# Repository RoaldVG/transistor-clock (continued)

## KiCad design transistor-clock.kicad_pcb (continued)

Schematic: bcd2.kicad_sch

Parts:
U5, U6: flipflop; module_flipflop_mpcie; LCSC Part # C185937

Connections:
+3V3: U5.21 (J), U5.25 (K), U6.21 (J), U6.25 (K); also elsewhere on the board
/counters/BCD_h0/Clr: U5.23 (Clk); also elsewhere on the board
/counters/BCD_h1/Clr: U5.29 (Clr), U6.29 (Clr), U6.31 (Q); also elsewhere on the board
/counters/BCD_h1/Q0: U5.31 (Q), U6.23 (Clk); also elsewhere on the board

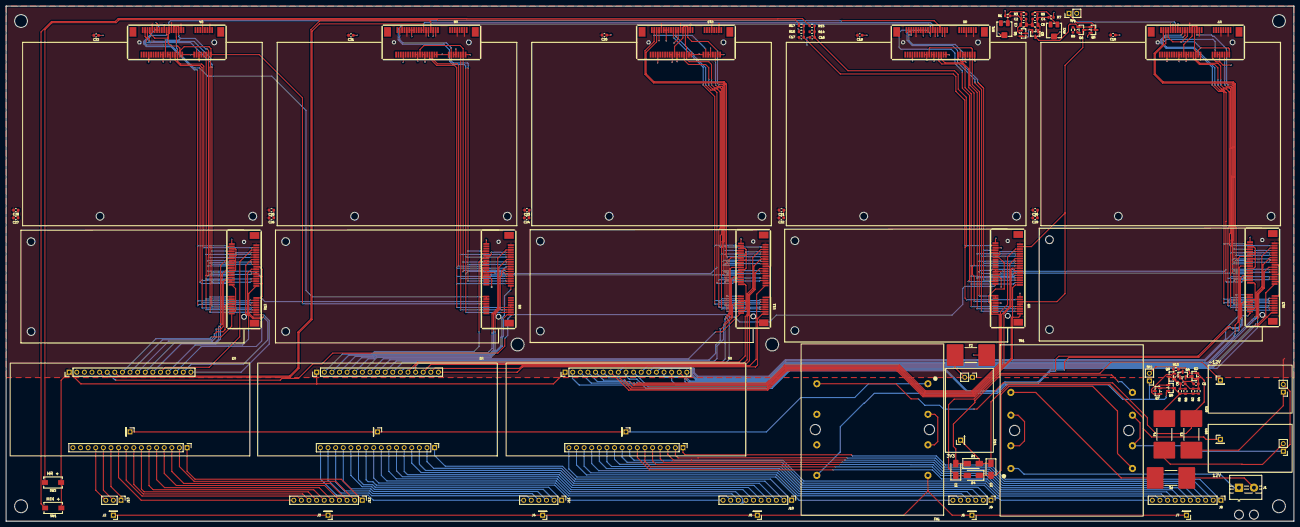
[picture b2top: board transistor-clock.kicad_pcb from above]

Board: 2 copper layers, 430.0 x 172.0 mm, 97 parts (0 on the bottom side), 174 nets.

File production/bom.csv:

Designator,Footprint,Quantity,Value,LCSC Part #
"C1, C6",0603,2,10n,C57112
"C16, C17, C18, C19, C20, C21, C22",0603,7,100n,C14663
"C2, C4",0603,2,1u,C15849
"C23, C24, C25, C26, C27, C28, C29, C30, C31, C32",0603,10,10u,C19702
"C3, C5",0805,2,47u,C16780
"D1, D2, D3, D4",D_SMA,4,S3MF,C64874
"F1, F3, F4",Fuse_Littelfuse-NANO2-885,3,250mA?,C41371860
F2,Fuse_Littelfuse-NANO2-885,1,2A?,C41371860
J1,TerminalBlock_MaiXu_MX126-5.0-02P_1x02_P5.00mm,1,Screw_Terminal_01x02,
"Q1, Q2, Q3, Q4, Q9",SOT-23,5,MMBT3904,C20526v
"Q5, Q7",SOT-23,2,AO3401A,C15127
"Q6, Q8",SOT-23,2,2N7002,C8545
"R1, R2, R3, R5, R7, R8",0603,6,15k,C22809
"R10, R15, R17, R9",0603,4,1k,C21190
"R14, R16",0603,2,10k,C25804
"R4, R6",0603,2,120k,C25808
"RV1, RV2",Potentiometer_Bourns_3214J_Horizontal,2,5k,C58391
SW1,SW_SPST_EVQPE1,1,MIN +,C720477
SW2,SW_SPST_EVQPE1,1,HR +,C720477
TP1,PinHeader_1x02_P2.54mm_Vertical,1,TestPoint_2Pole,
"U1, U2, U3",module_ssr,3,SSR,
"U10, U4, U5, U6, U7",module_flipflop_mpcie,5,flipflop,C185937
"U11, U12, U13, U8, U9",module_bdc_mpcie,5,bin-to-dec,C185937
U14,module_PSU,1,3V3,
U15,module_PSU,1,12V,
U16,module_PSU,1,-12V,

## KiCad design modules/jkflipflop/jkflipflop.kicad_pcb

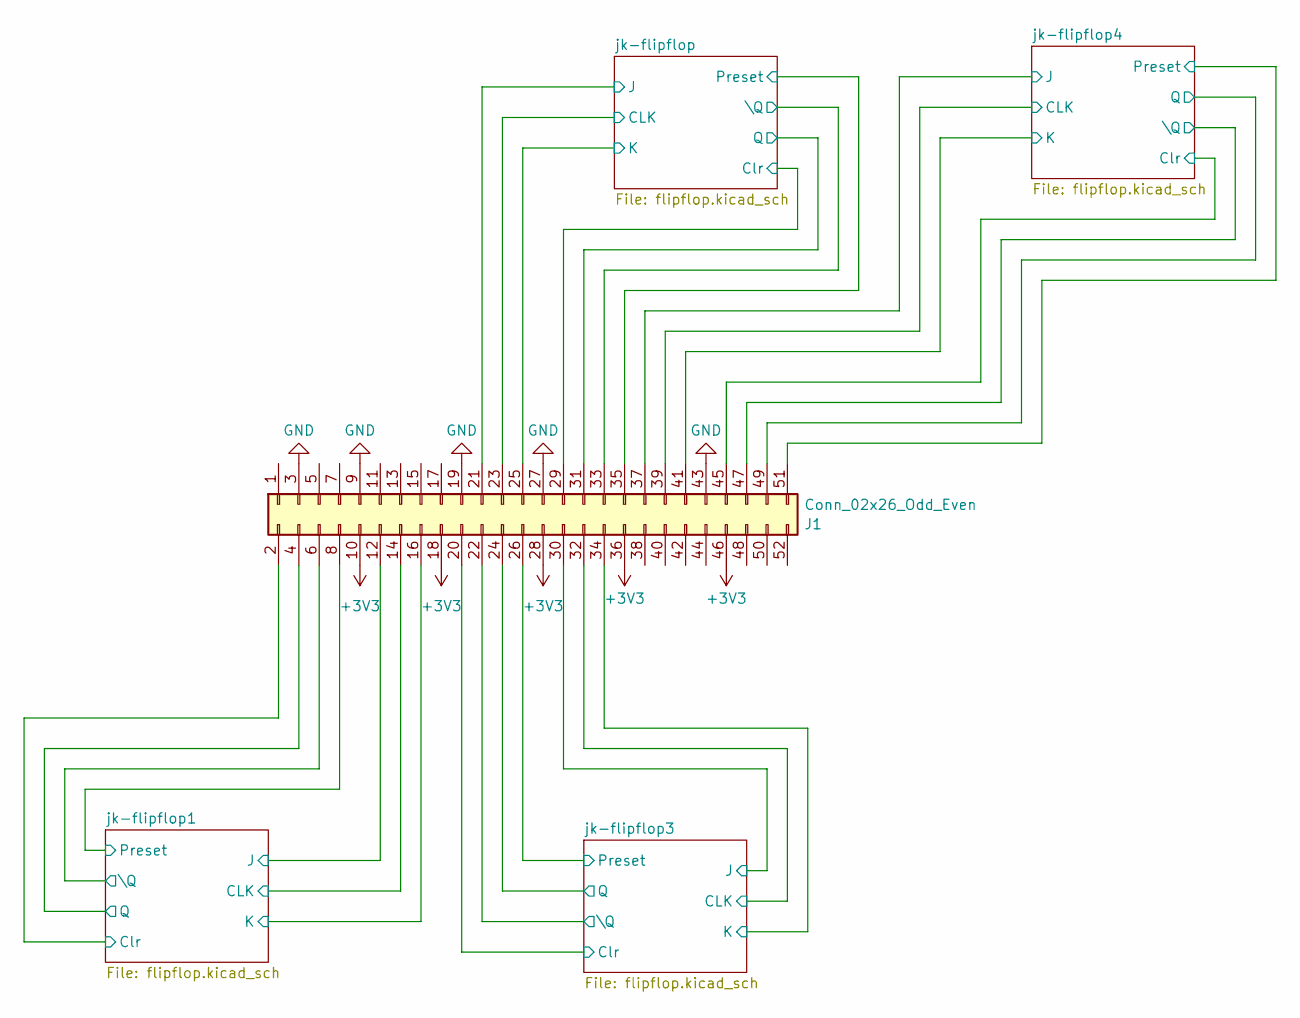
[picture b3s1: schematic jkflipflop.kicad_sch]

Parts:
J1: Conn_02x26_Odd_Even; mpcie-full-card

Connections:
+3V3: J1.10, J1.18, J1.28, J1.36, J1.46; also elsewhere on the board
/jk-flipflop1/CLK: J1.14; also elsewhere on the board
/jk-flipflop1/Clr: J1.2; also elsewhere on the board
/jk-flipflop1/J: J1.12; also elsewhere on the board
/jk-flipflop1/K: J1.16; also elsewhere on the board
/jk-flipflop1/Preset: J1.8; also elsewhere on the board
/jk-flipflop1/Q: J1.4; also elsewhere on the board
/jk-flipflop1/\Q: J1.6; also elsewhere on the board
/jk-flipflop3/CLK: J1.32; also elsewhere on the board
/jk-flipflop3/Clr: J1.20; also elsewhere on the board
/jk-flipflop3/J: J1.30; also elsewhere on the board
/jk-flipflop3/K: J1.34; also elsewhere on the board
/jk-flipflop3/Preset: J1.26; also elsewhere on the board
/jk-flipflop3/Q: J1.24; also elsewhere on the board
/jk-flipflop3/\Q: J1.22; also elsewhere on the board
/jk-flipflop4/CLK: J1.39; also elsewhere on the board
/jk-flipflop4/Clr: J1.45; also elsewhere on the board
/jk-flipflop4/J: J1.37; also elsewhere on the board
/jk-flipflop4/K: J1.41; also elsewhere on the board
/jk-flipflop4/Preset: J1.51; also elsewhere on the board
/jk-flipflop4/Q: J1.49; also elsewhere on the board
/jk-flipflop4/\Q: J1.47; also elsewhere on the board
/jk-flipflop/CLK: J1.23; also elsewhere on the board
/jk-flipflop/Clr: J1.29; also elsewhere on the board
/jk-flipflop/J: J1.21; also elsewhere on the board
/jk-flipflop/K: J1.25; also elsewhere on the board
/jk-flipflop/Preset: J1.35; also elsewhere on the board
/jk-flipflop/Q: J1.31; also elsewhere on the board
/jk-flipflop/\Q: J1.33; also elsewhere on the board
GND: J1.3, J1.9, J1.19, J1.27, J1.43; also elsewhere on the board

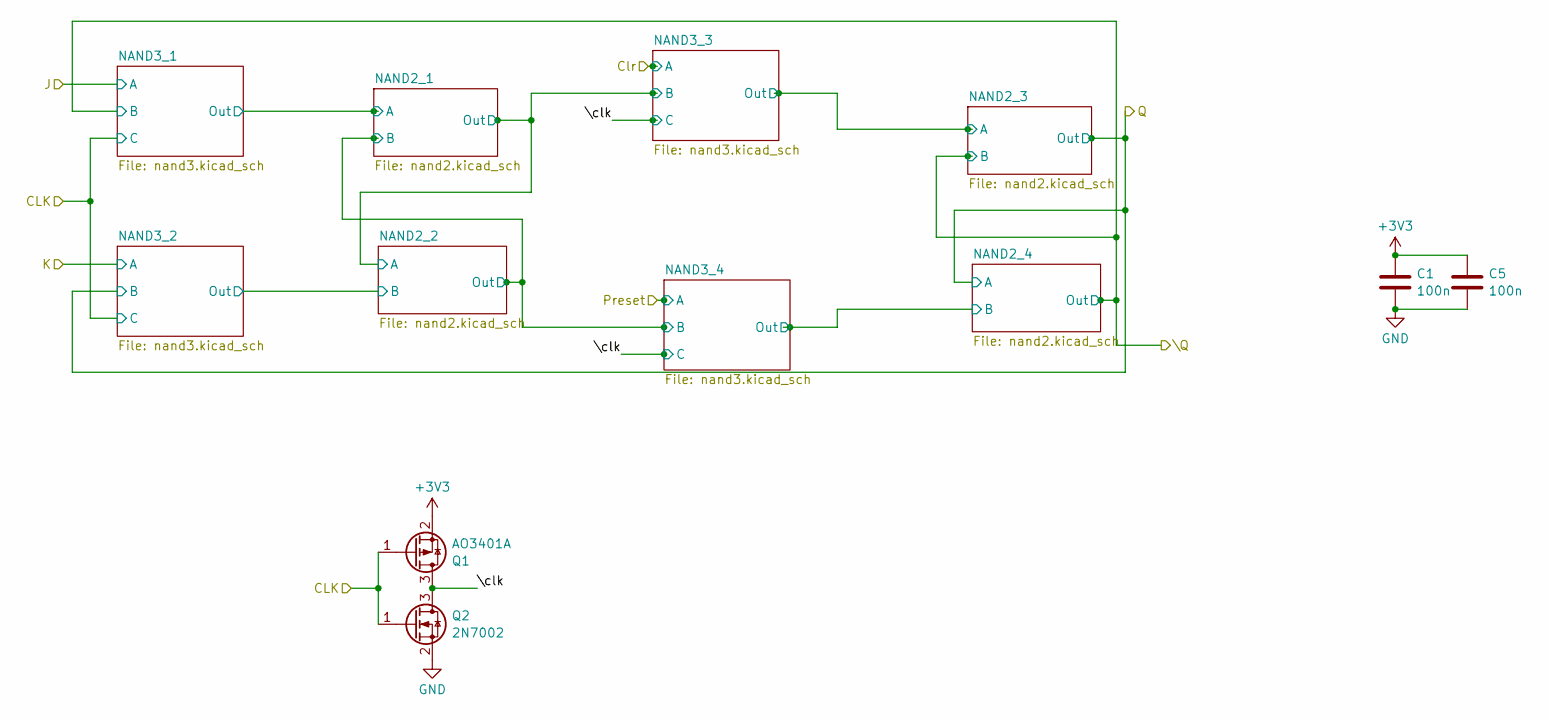
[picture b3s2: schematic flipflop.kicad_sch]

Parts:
C1, C5: 100n; C_0603_1608Metric; LCSC Part # C14663
Q1: AO3401A; SOT-23; LCSC Part # C15127
Q2: 2N7002; SOT-23; LCSC Part # C8545

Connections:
+3V3: C1.1, C5.1, Q1.2 (S); also elsewhere on the board
/jk-flipflop1/CLK: Q1.1 (G), Q2.1 (G); also elsewhere on the board
/jk-flipflop1/\clk: Q1.3 (D), Q2.3 (D); also elsewhere on the board
GND: C1.2, C5.2, Q2.2 (S); also elsewhere on the board

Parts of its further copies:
C2, C3, C4, C6, C7, C8: 100n; C_0603_1608Metric; LCSC Part # C14663
Q21, Q57, Q77: AO3401A; SOT-23; LCSC Part # C15127
Q22, Q58, Q78: 2N7002; SOT-23; LCSC Part # C8545

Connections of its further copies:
+3V3: C2.1, C3.1, C4.1, C6.1, C7.1, C8.1, Q21.2 (S), Q57.2 (S), Q77.2 (S); also elsewhere on the board
/jk-flipflop3/CLK: Q77.1 (G), Q78.1 (G); also elsewhere on the board
/jk-flipflop3/\clk: Q77.3 (D), Q78.3 (D); also elsewhere on the board
/jk-flipflop4/CLK: Q57.1 (G), Q58.1 (G); also elsewhere on the board
/jk-flipflop4/\clk: Q57.3 (D), Q58.3 (D); also elsewhere on the board
/jk-flipflop/CLK: Q21.1 (G), Q22.1 (G); also elsewhere on the board
/jk-flipflop/\clk: Q21.3 (D), Q22.3 (D); also elsewhere on the board
GND: C2.2, C3.2, C4.2, C6.2, C7.2, C8.2, Q22.2 (S), Q58.2 (S), Q78.2 (S); also elsewhere on the board

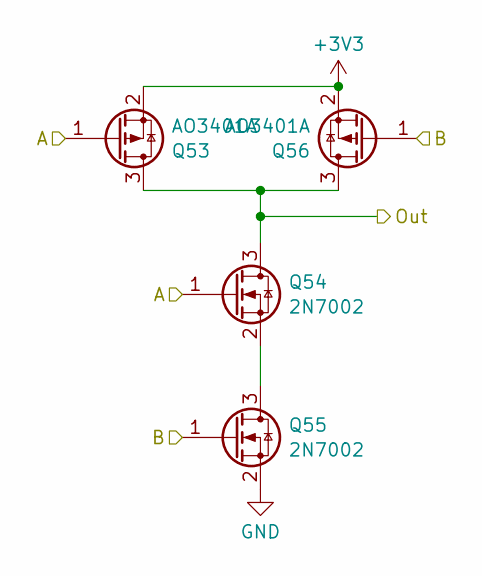
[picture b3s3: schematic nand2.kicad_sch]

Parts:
Q53, Q56: AO3401A; SOT-23; LCSC Part # C15127
Q54, Q55: 2N7002; SOT-23; LCSC Part # C8545

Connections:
+3V3: Q53.2 (S), Q56.2 (S); also elsewhere on the board
/jk-flipflop1/NAND2_1/B: Q53.3 (D), Q54.3 (D), Q56.3 (D); also elsewhere on the board
/jk-flipflop1/NAND2_1/Out: Q53.1 (G), Q54.1 (G); also elsewhere on the board
/jk-flipflop1/NAND2_2/B: Q55.1 (G), Q56.1 (G); also elsewhere on the board
GND: Q55.2 (S); also elsewhere on the board
unnamed: Q54.2 (S), Q55.3 (D)

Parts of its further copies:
Q104, Q111, Q113, Q116, Q117, Q120, Q121, Q124, Q125, Q128, Q129, Q132, Q133, Q136, Q137, Q140, Q141, Q144, Q145, Q148, Q149, Q152, Q153, Q156, Q157, Q160, Q161, Q164, Q165, Q168: AO3401A; SOT-23; LCSC Part # C15127
Q108, Q109, Q114, Q115, Q118, Q119, Q122, Q123, Q126, Q127, Q130, Q131, Q134, Q135, Q138, Q139, Q142, Q143, Q146, Q147, Q150, Q151, Q154, Q155, Q158, Q159, Q162, Q163, Q166, Q167: 2N7002; SOT-23; LCSC Part # C8545

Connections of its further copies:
+3V3: Q104.2 (S), Q111.2 (S), Q113.2 (S), Q116.2 (S), Q117.2 (S), Q120.2 (S), Q121.2 (S), Q124.2 (S), Q125.2 (S), Q128.2 (S), Q129.2 (S), Q132.2 (S), Q133.2 (S), Q136.2 (S), Q137.2 (S), Q140.2 (S), Q141.2 (S), Q144.2 (S), Q145.2 (S), Q148.2 (S), Q149.2 (S), Q152.2 (S), Q153.2 (S), Q156.2 (S), Q157.2 (S), Q160.2 (S), Q161.2 (S), Q164.2 (S), Q165.2 (S), Q168.2 (S); also elsewhere on the board
/jk-flipflop1/NAND2_1/A: Q157.1 (G), Q158.1 (G); also elsewhere on the board
/jk-flipflop1/NAND2_1/B: Q159.1 (G), Q160.1 (G); also elsewhere on the board
/jk-flipflop1/NAND2_1/Out: Q157.3 (D), Q158.3 (D), Q160.3 (D); also elsewhere on the board
/jk-flipflop1/NAND2_3/A: Q125.1 (G), Q126.1 (G); also elsewhere on the board
/jk-flipflop1/NAND2_4/B: Q131.1 (G), Q132.1 (G); also elsewhere on the board
/jk-flipflop1/Q: Q125.3 (D), Q126.3 (D), Q128.3 (D), Q129.1 (G), Q130.1 (G); also elsewhere on the board
/jk-flipflop1/\Q: Q127.1 (G), Q128.1 (G), Q129.3 (D), Q130.3 (D), Q132.3 (D); also elsewhere on the board
/jk-flipflop3/NAND2_1/A: Q161.1 (G), Q162.1 (G); also elsewhere on the board
/jk-flipflop3/NAND2_1/B: Q121.3 (D), Q122.3 (D), Q124.3 (D), Q163.1 (G), Q164.1 (G); also elsewhere on the board
/jk-flipflop3/NAND2_1/Out: Q121.1 (G), Q122.1 (G), Q161.3 (D), Q162.3 (D), Q164.3 (D); also elsewhere on the board
/jk-flipflop3/NAND2_2/B: Q123.1 (G), Q124.1 (G); also elsewhere on the board
/jk-flipflop3/NAND2_3/A: Q149.1 (G), Q150.1 (G); also elsewhere on the board
/jk-flipflop3/NAND2_4/B: Q155.1 (G), Q156.1 (G); also elsewhere on the board
/jk-flipflop3/Q: Q149.3 (D), Q150.3 (D), Q152.3 (D), Q153.1 (G), Q154.1 (G); also elsewhere on the board
/jk-flipflop3/\Q: Q151.1 (G), Q152.1 (G), Q153.3 (D), Q154.3 (D), Q156.3 (D); also elsewhere on the board
/jk-flipflop4/NAND2_1/A: Q165.1 (G), Q166.1 (G); also elsewhere on the board
/jk-flipflop4/NAND2_1/B: Q117.3 (D), Q118.3 (D), Q120.3 (D), Q167.1 (G), Q168.1 (G); also elsewhere on the board
/jk-flipflop4/NAND2_1/Out: Q117.1 (G), Q118.1 (G), Q165.3 (D), Q166.3 (D), Q168.3 (D); also elsewhere on the board
/jk-flipflop4/NAND2_2/B: Q119.1 (G), Q120.1 (G); also elsewhere on the board
/jk-flipflop4/NAND2_3/A: Q141.1 (G), Q142.1 (G); also elsewhere on the board
/jk-flipflop4/NAND2_4/B: Q147.1 (G), Q148.1 (G); also elsewhere on the board
/jk-flipflop4/Q: Q141.3 (D), Q142.3 (D), Q144.3 (D), Q145.1 (G), Q146.1 (G); also elsewhere on the board
/jk-flipflop4/\Q: Q143.1 (G), Q144.1 (G), Q145.3 (D), Q146.3 (D), Q148.3 (D); also elsewhere on the board
/jk-flipflop/NAND2_1/A: Q104.1 (G), Q108.1 (G); also elsewhere on the board
/jk-flipflop/NAND2_1/B: Q109.1 (G), Q111.1 (G), Q113.3 (D), Q114.3 (D), Q116.3 (D); also elsewhere on the board
/jk-flipflop/NAND2_1/Out: Q104.3 (D), Q108.3 (D), Q111.3 (D), Q113.1 (G), Q114.1 (G); also elsewhere on the board
/jk-flipflop/NAND2_2/B: Q115.1 (G), Q116.1 (G); also elsewhere on the board
/jk-flipflop/NAND2_3/A: Q133.1 (G), Q134.1 (G); also elsewhere on the board
/jk-flipflop/NAND2_4/B: Q139.1 (G), Q140.1 (G); also elsewhere on the board
/jk-flipflop/Q: Q133.3 (D), Q134.3 (D), Q136.3 (D), Q137.1 (G), Q138.1 (G); also elsewhere on the board
/jk-flipflop/\Q: Q135.1 (G), Q136.1 (G), Q137.3 (D), Q138.3 (D), Q140.3 (D); also elsewhere on the board
GND: Q109.2 (S), Q115.2 (S), Q119.2 (S), Q123.2 (S), Q127.2 (S), Q131.2 (S), Q135.2 (S), Q139.2 (S), Q143.2 (S), Q147.2 (S), Q151.2 (S), Q155.2 (S), Q159.2 (S), Q163.2 (S), Q167.2 (S); also elsewhere on the board
unnamed: Q108.2 (S), Q109.3 (D)
unnamed: Q114.2 (S), Q115.3 (D)
unnamed: Q118.2 (S), Q119.3 (D)
unnamed: Q122.2 (S), Q123.3 (D)
unnamed: Q126.2 (S), Q127.3 (D)
unnamed: Q130.2 (S), Q131.3 (D)
unnamed: Q134.2 (S), Q135.3 (D)
unnamed: Q138.2 (S), Q139.3 (D)
unnamed: Q142.2 (S), Q143.3 (D)
unnamed: Q146.2 (S), Q147.3 (D)
unnamed: Q150.2 (S), Q151.3 (D)
unnamed: Q154.2 (S), Q155.3 (D)
unnamed: Q158.2 (S), Q159.3 (D)
unnamed: Q162.2 (S), Q163.3 (D)
unnamed: Q166.2 (S), Q167.3 (D)

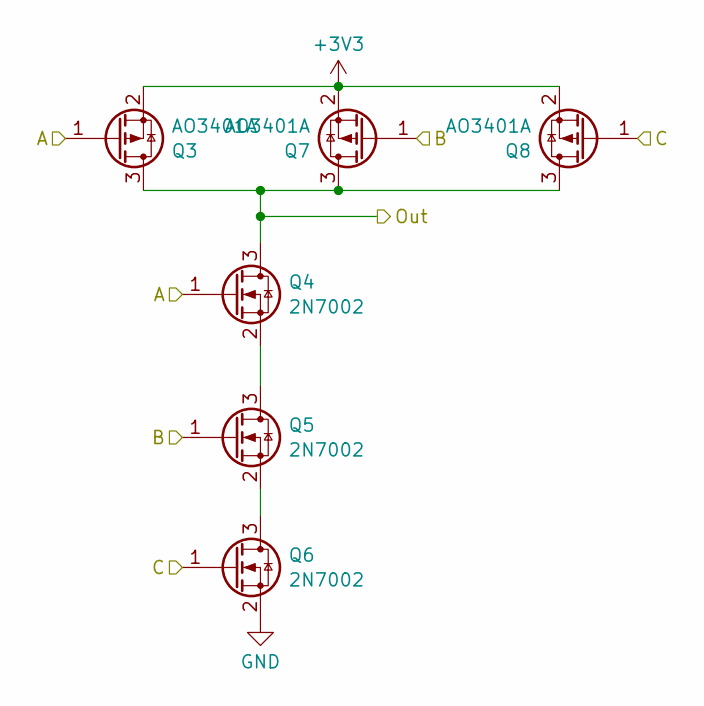
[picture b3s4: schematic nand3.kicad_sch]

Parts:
Q3, Q7, Q8: AO3401A; SOT-23; LCSC Part # C15127
Q4, Q5, Q6: 2N7002; SOT-23; LCSC Part # C8545

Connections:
+3V3: Q3.2 (S), Q7.2 (S), Q8.2 (S); also elsewhere on the board
/jk-flipflop1/CLK: Q6.1 (G), Q8.1 (G); also elsewhere on the board
/jk-flipflop1/K: Q3.1 (G), Q4.1 (G); also elsewhere on the board
/jk-flipflop1/NAND2_2/B: Q3.3 (D), Q4.3 (D), Q7.3 (D), Q8.3 (D); also elsewhere on the board
/jk-flipflop1/Q: Q5.1 (G), Q7.1 (G); also elsewhere on the board
GND: Q6.2 (S); also elsewhere on the board
unnamed: Q4.2 (S), Q5.3 (D)
unnamed: Q5.2 (S), Q6.3 (D)

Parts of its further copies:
Q9, Q13, Q14, Q15, Q19, Q20, Q23, Q27, Q28, Q29, Q33, Q34, Q35, Q39, Q40, Q41, Q45, Q46, Q47, Q51, Q52, Q59, Q63, Q64, Q65, Q69, Q70, Q71, Q75, Q76, Q79, Q83, Q84, Q85, Q89, Q90, Q91, Q95, Q96, Q97, Q101, Q102, Q103, Q110, Q112: AO3401A; SOT-23; LCSC Part # C15127
Q10, Q11, Q12, Q16, Q17, Q18, Q24, Q25, Q26, Q30, Q31, Q32, Q36, Q37, Q38, Q42, Q43, Q44, Q48, Q49, Q50, Q60, Q61, Q62, Q66, Q67, Q68, Q72, Q73, Q74, Q80, Q81, Q82, Q86, Q87, Q88, Q92, Q93, Q94, Q98, Q99, Q100, Q105, Q106, Q107: 2N7002; SOT-23; LCSC Part # C8545

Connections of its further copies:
+3V3: Q9.2 (S), Q13.2 (S), Q14.2 (S), Q15.2 (S), Q19.2 (S), Q20.2 (S), Q23.2 (S), Q27.2 (S), Q28.2 (S), Q29.2 (S), Q33.2 (S), Q34.2 (S), Q35.2 (S), Q39.2 (S), Q40.2 (S), Q41.2 (S), Q45.2 (S), Q46.2 (S), Q47.2 (S), Q51.2 (S), Q52.2 (S), Q59.2 (S), Q63.2 (S), Q64.2 (S), Q65.2 (S), Q69.2 (S), Q70.2 (S), Q71.2 (S), Q75.2 (S), Q76.2 (S), Q79.2 (S), Q83.2 (S), Q84.2 (S), Q85.2 (S), Q89.2 (S), Q90.2 (S), Q91.2 (S), Q95.2 (S), Q96.2 (S), Q97.2 (S), Q101.2 (S), Q102.2 (S), Q103.2 (S), Q110.2 (S), Q112.2 (S); also elsewhere on the board
/jk-flipflop1/CLK: Q12.1 (G), Q14.1 (G); also elsewhere on the board
/jk-flipflop1/Clr: Q15.1 (G), Q16.1 (G); also elsewhere on the board
/jk-flipflop1/J: Q9.1 (G), Q10.1 (G); also elsewhere on the board
/jk-flipflop1/NAND2_1/A: Q9.3 (D), Q10.3 (D), Q13.3 (D), Q14.3 (D); also elsewhere on the board
/jk-flipflop1/NAND2_1/B: Q49.1 (G), Q51.1 (G); also elsewhere on the board
/jk-flipflop1/NAND2_1/Out: Q17.1 (G), Q19.1 (G); also elsewhere on the board
/jk-flipflop1/NAND2_3/A: Q15.3 (D), Q16.3 (D), Q19.3 (D), Q20.3 (D); also elsewhere on the board
/jk-flipflop1/NAND2_4/B: Q47.3 (D), Q48.3 (D), Q51.3 (D), Q52.3 (D); also elsewhere on the board
/jk-flipflop1/Preset: Q47.1 (G), Q48.1 (G); also elsewhere on the board
/jk-flipflop1/\Q: Q11.1 (G), Q13.1 (G); also elsewhere on the board
/jk-flipflop1/\clk: Q18.1 (G), Q20.1 (G), Q50.1 (G), Q52.1 (G); also elsewhere on the board
/jk-flipflop3/CLK: Q82.1 (G), Q84.1 (G), Q88.1 (G), Q90.1 (G); also elsewhere on the board
/jk-flipflop3/Clr: Q91.1 (G), Q92.1 (G); also elsewhere on the board
/jk-flipflop3/J: Q85.1 (G), Q86.1 (G); also elsewhere on the board
/jk-flipflop3/K: Q79.1 (G), Q80.1 (G); also elsewhere on the board
/jk-flipflop3/NAND2_1/A: Q85.3 (D), Q86.3 (D), Q89.3 (D), Q90.3 (D); also elsewhere on the board
/jk-flipflop3/NAND2_1/B: Q99.1 (G), Q101.1 (G); also elsewhere on the board
/jk-flipflop3/NAND2_1/Out: Q93.1 (G), Q95.1 (G); also elsewhere on the board
/jk-flipflop3/NAND2_2/B: Q79.3 (D), Q80.3 (D), Q83.3 (D), Q84.3 (D); also elsewhere on the board
/jk-flipflop3/NAND2_3/A: Q91.3 (D), Q92.3 (D), Q95.3 (D), Q96.3 (D); also elsewhere on the board
/jk-flipflop3/NAND2_4/B: Q97.3 (D), Q98.3 (D), Q101.3 (D), Q102.3 (D); also elsewhere on the board
/jk-flipflop3/Preset: Q97.1 (G), Q98.1 (G); also elsewhere on the board
/jk-flipflop3/Q: Q81.1 (G), Q83.1 (G); also elsewhere on the board
/jk-flipflop3/\Q: Q87.1 (G), Q89.1 (G); also elsewhere on the board
/jk-flipflop3/\clk: Q94.1 (G), Q96.1 (G), Q100.1 (G), Q102.1 (G); also elsewhere on the board
/jk-flipflop4/CLK: Q74.1 (G), Q76.1 (G), Q107.1 (G), Q112.1 (G); also elsewhere on the board
/jk-flipflop4/Clr: Q59.1 (G), Q60.1 (G); also elsewhere on the board
/jk-flipflop4/J: Q71.1 (G), Q72.1 (G); also elsewhere on the board
/jk-flipflop4/K: Q103.1 (G), Q105.1 (G); also elsewhere on the board
/jk-flipflop4/NAND2_1/A: Q71.3 (D), Q72.3 (D), Q75.3 (D), Q76.3 (D); also elsewhere on the board
/jk-flipflop4/NAND2_1/B: Q67.1 (G), Q69.1 (G); also elsewhere on the board
/jk-flipflop4/NAND2_1/Out: Q61.1 (G), Q63.1 (G); also elsewhere on the board
/jk-flipflop4/NAND2_2/B: Q103.3 (D), Q105.3 (D), Q110.3 (D), Q112.3 (D); also elsewhere on the board
/jk-flipflop4/NAND2_3/A: Q59.3 (D), Q60.3 (D), Q63.3 (D), Q64.3 (D); also elsewhere on the board
/jk-flipflop4/NAND2_4/B: Q65.3 (D), Q66.3 (D), Q69.3 (D), Q70.3 (D); also elsewhere on the board
/jk-flipflop4/Preset: Q65.1 (G), Q66.1 (G); also elsewhere on the board
/jk-flipflop4/Q: Q106.1 (G), Q110.1 (G); also elsewhere on the board
/jk-flipflop4/\Q: Q73.1 (G), Q75.1 (G); also elsewhere on the board
/jk-flipflop4/\clk: Q62.1 (G), Q64.1 (G), Q68.1 (G), Q70.1 (G); also elsewhere on the board
/jk-flipflop/CLK: Q26.1 (G), Q28.1 (G), Q32.1 (G), Q34.1 (G); also elsewhere on the board
/jk-flipflop/Clr: Q35.1 (G), Q36.1 (G); also elsewhere on the board
/jk-flipflop/J: Q23.1 (G), Q24.1 (G); also elsewhere on the board
/jk-flipflop/K: Q29.1 (G), Q30.1 (G); also elsewhere on the board
/jk-flipflop/NAND2_1/A: Q23.3 (D), Q24.3 (D), Q27.3 (D), Q28.3 (D); also elsewhere on the board
/jk-flipflop/NAND2_1/B: Q43.1 (G), Q45.1 (G); also elsewhere on the board
/jk-flipflop/NAND2_1/Out: Q37.1 (G), Q39.1 (G); also elsewhere on the board
/jk-flipflop/NAND2_2/B: Q29.3 (D), Q30.3 (D), Q33.3 (D), Q34.3 (D); also elsewhere on the board
/jk-flipflop/NAND2_3/A: Q35.3 (D), Q36.3 (D), Q39.3 (D), Q40.3 (D); also elsewhere on the board
/jk-flipflop/NAND2_4/B: Q41.3 (D), Q42.3 (D), Q45.3 (D), Q46.3 (D); also elsewhere on the board
/jk-flipflop/Preset: Q41.1 (G), Q42.1 (G); also elsewhere on the board
/jk-flipflop/Q: Q31.1 (G), Q33.1 (G); also elsewhere on the board
/jk-flipflop/\Q: Q25.1 (G), Q27.1 (G); also elsewhere on the board
/jk-flipflop/\clk: Q38.1 (G), Q40.1 (G), Q44.1 (G), Q46.1 (G); also elsewhere on the board
GND: Q12.2 (S), Q18.2 (S), Q26.2 (S), Q32.2 (S), Q38.2 (S), Q44.2 (S), Q50.2 (S), Q62.2 (S), Q68.2 (S), Q74.2 (S), Q82.2 (S), Q88.2 (S), Q94.2 (S), Q100.2 (S), Q107.2 (S); also elsewhere on the board
unnamed: Q10.2 (S), Q11.3 (D)
unnamed: Q11.2 (S), Q12.3 (D)
unnamed: Q16.2 (S), Q17.3 (D)
unnamed: Q17.2 (S), Q18.3 (D)
unnamed: Q24.2 (S), Q25.3 (D)
unnamed: Q25.2 (S), Q26.3 (D)
unnamed: Q30.2 (S), Q31.3 (D)
unnamed: Q31.2 (S), Q32.3 (D)
unnamed: Q36.2 (S), Q37.3 (D)
unnamed: Q37.2 (S), Q38.3 (D)
unnamed: Q42.2 (S), Q43.3 (D)
unnamed: Q43.2 (S), Q44.3 (D)
unnamed: Q48.2 (S), Q49.3 (D)
unnamed: Q49.2 (S), Q50.3 (D)
unnamed: Q60.2 (S), Q61.3 (D)
unnamed: Q61.2 (S), Q62.3 (D)
unnamed: Q66.2 (S), Q67.3 (D)
unnamed: Q67.2 (S), Q68.3 (D)
unnamed: Q72.2 (S), Q73.3 (D)
unnamed: Q73.2 (S), Q74.3 (D)
unnamed: Q80.2 (S), Q81.3 (D)
unnamed: Q81.2 (S), Q82.3 (D)
unnamed: Q86.2 (S), Q87.3 (D)
unnamed: Q87.2 (S), Q88.3 (D)
unnamed: Q92.2 (S), Q93.3 (D)
unnamed: Q93.2 (S), Q94.3 (D)
unnamed: Q98.2 (S), Q99.3 (D)
unnamed: Q99.2 (S), Q100.3 (D)
unnamed: Q105.2 (S), Q106.3 (D)
unnamed: Q106.2 (S), Q107.3 (D)

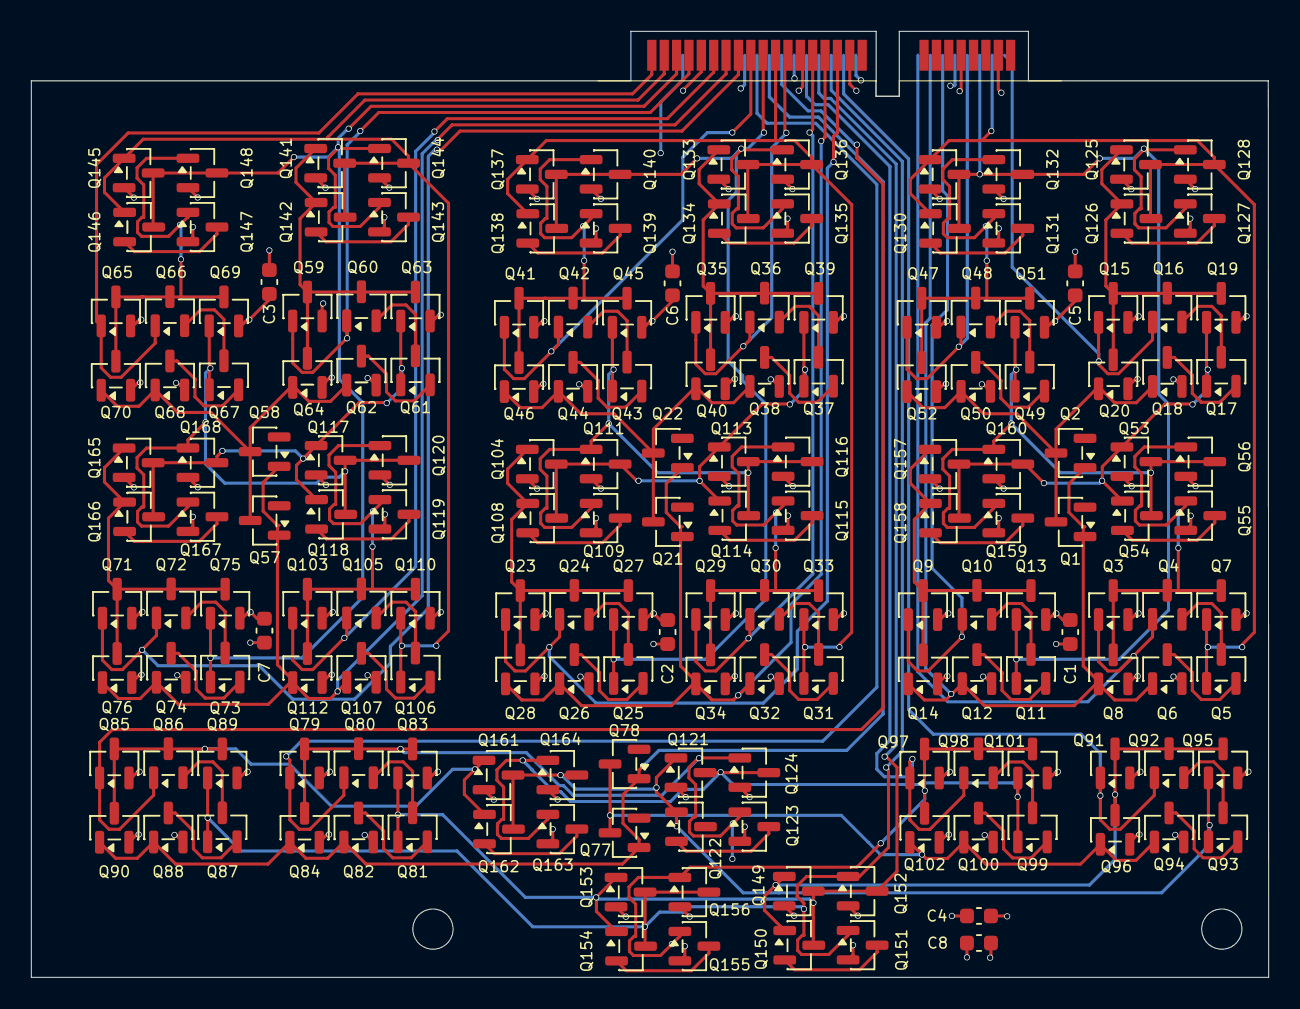
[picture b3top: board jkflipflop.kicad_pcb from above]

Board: 4 copper layers, 80.0 x 61.2 mm, 177 parts (0 on the bottom side), 106 nets.

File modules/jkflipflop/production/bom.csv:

Designator,Footprint,Quantity,Value,LCSC Part #
"C1, C2, C3, C4, C5, C6, C7, C8",0603,8,100n,C14663
"Q1, Q101, Q102, Q103, Q104, Q110, Q111, Q112, Q113, Q116, Q117, Q120, Q121, Q124, Q125, Q128, Q129, Q13, Q132, Q133, Q136, Q137, Q14, Q140, Q141, Q144, Q145, Q148, Q149, Q15, Q152, Q153, Q156, Q157, Q160, Q161, Q164, Q165, Q168, Q19, Q20, Q21, Q23, Q27, Q28, Q29, Q3, Q33, Q34, Q35, Q39, Q40, Q41, Q45, Q46, Q47, Q51, Q52, Q53, Q56, Q57, Q59, Q63, Q64, Q65, Q69, Q7, Q70, Q71, Q75, Q76, Q77, Q79, Q8, Q83, Q84, Q85, Q89, Q9, Q90, Q91, Q95, Q96, Q97",SOT-23,84,AO3401A,C15127
"Q10, Q100, Q105, Q106, Q107, Q108, Q109, Q11, Q114, Q115, Q118, Q119, Q12, Q122, Q123, Q126, Q127, Q130, Q131, Q134, Q135, Q138, Q139, Q142, Q143, Q146, Q147, Q150, Q151, Q154, Q155, Q158, Q159, Q16, Q162, Q163, Q166, Q167, Q17, Q18, Q2, Q22, Q24, Q25, Q26, Q30, Q31, Q32, Q36, Q37, Q38, Q4, Q42, Q43, Q44, Q48, Q49, Q5, Q50, Q54, Q55, Q58, Q6, Q60, Q61, Q62, Q66, Q67, Q68, Q72, Q73, Q74, Q78, Q80, Q81, Q82, Q86, Q87, Q88, Q92, Q93, Q94, Q98, Q99",SOT-23,84,2N7002,C8545

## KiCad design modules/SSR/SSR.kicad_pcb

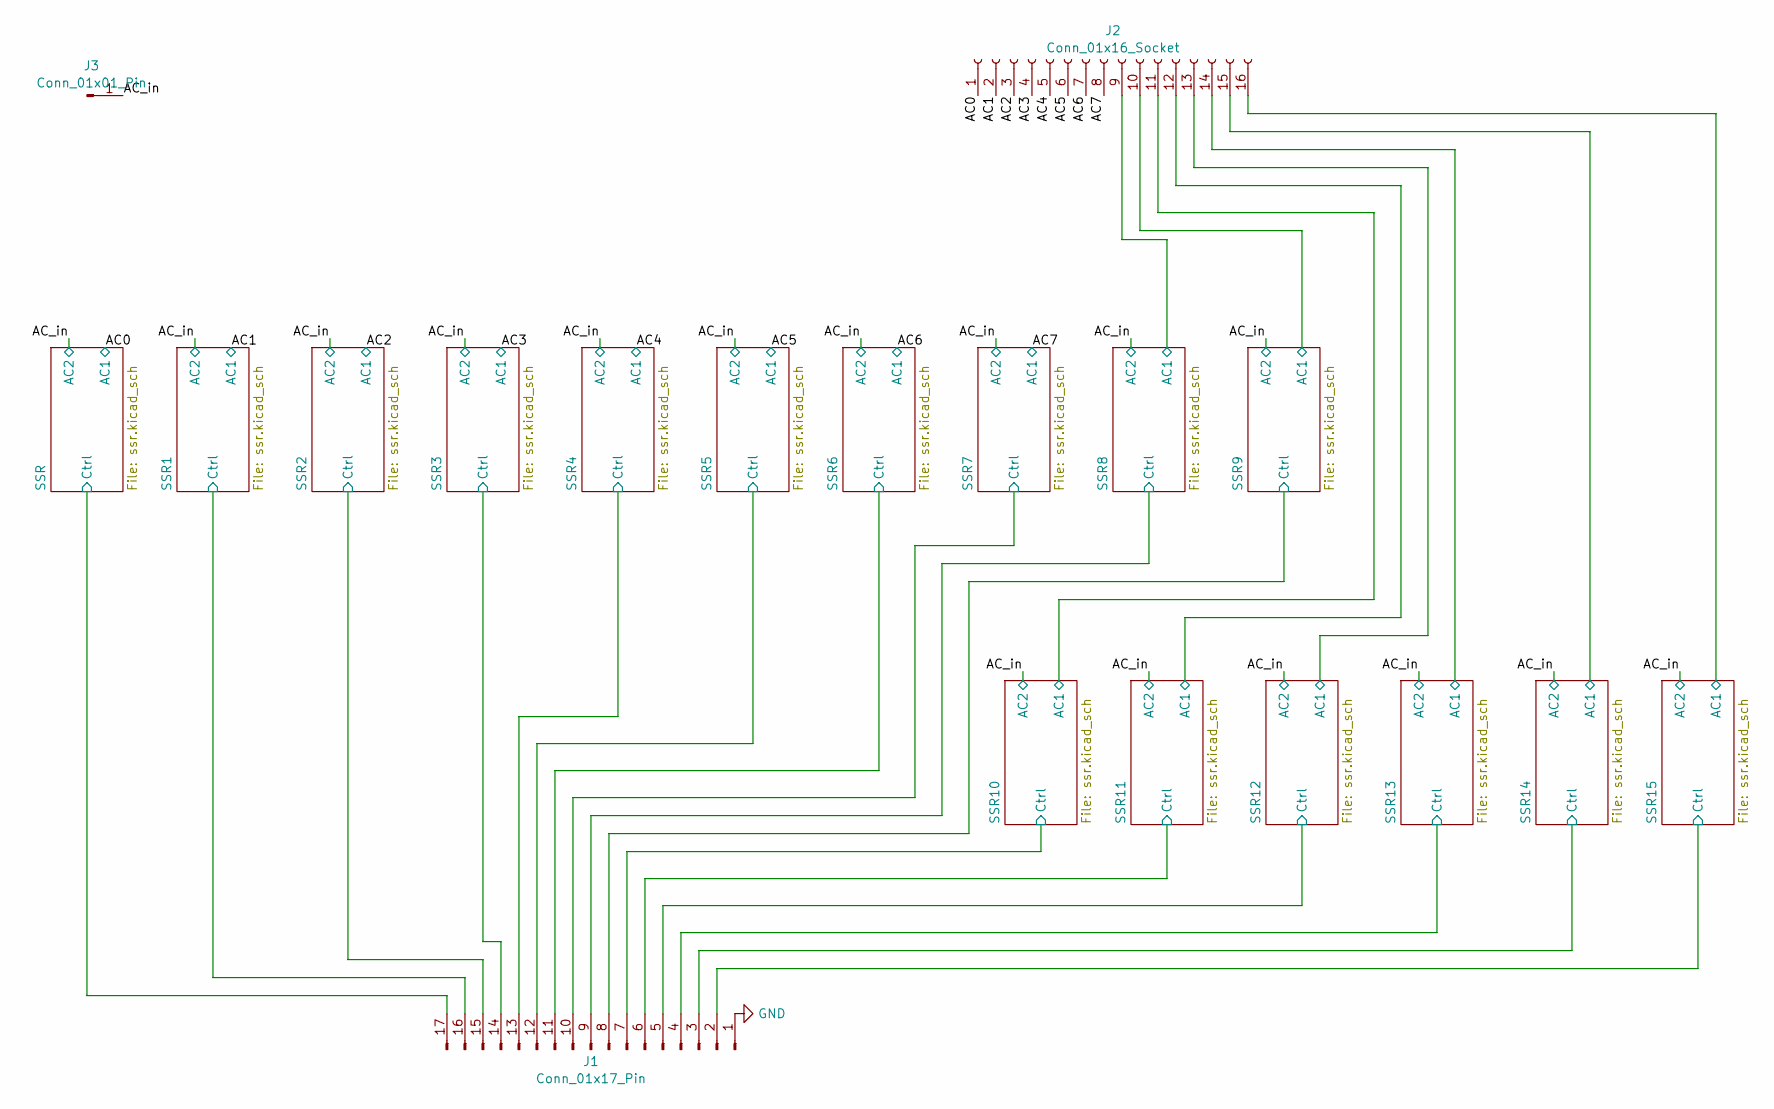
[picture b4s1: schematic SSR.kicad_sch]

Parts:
J1: Conn_01x17_Pin; PinHeader_1x17_P2.54mm_Vertical
J2: Conn_01x16_Socket; PinHeader_1x16_P2.54mm_Vertical
J3: Conn_01x01_Pin; PinHeader_1x01_P2.54mm_Vertical

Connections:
/AC0: J2.1; also elsewhere on the board
/AC1: J2.2; also elsewhere on the board
/AC2: J2.3; also elsewhere on the board
/AC3: J2.4; also elsewhere on the board
/AC4: J2.5; also elsewhere on the board
/AC5: J2.6; also elsewhere on the board
/AC6: J2.7; also elsewhere on the board
/AC7: J2.8; also elsewhere on the board
/AC_in: J3.1; also elsewhere on the board
/SSR1/Ctrl: J1.16; also elsewhere on the board
/SSR2/Ctrl: J1.15; also elsewhere on the board
/SSR3/Ctrl: J1.14; also elsewhere on the board
/SSR4/Ctrl: J1.13; also elsewhere on the board
/SSR5/Ctrl: J1.12; also elsewhere on the board
/SSR6/Ctrl: J1.11; also elsewhere on the board
/SSR7/Ctrl: J1.10; also elsewhere on the board
/SSR8/AC1: J2.9; also elsewhere on the board
/SSR8/Ctrl: J1.9; also elsewhere on the board
/SSR9/AC1: J2.10; also elsewhere on the board
/SSR9/Ctrl: J1.8; also elsewhere on the board
/SSR10/AC1: J2.11; also elsewhere on the board
/SSR10/Ctrl: J1.7; also elsewhere on the board
/SSR11/AC1: J2.12; also elsewhere on the board
/SSR11/Ctrl: J1.6; also elsewhere on the board
/SSR12/AC1: J2.13; also elsewhere on the board
/SSR12/Ctrl: J1.5; also elsewhere on the board
/SSR13/AC1: J2.14; also elsewhere on the board
/SSR13/Ctrl: J1.4; also elsewhere on the board
/SSR14/AC1: J2.15; also elsewhere on the board
/SSR14/Ctrl: J1.3; also elsewhere on the board
/SSR15/AC1: J2.16; also elsewhere on the board
/SSR15/Ctrl: J1.2; also elsewhere on the board
/SSR/Ctrl: J1.17; also elsewhere on the board
GND: J1.1; also elsewhere on the board

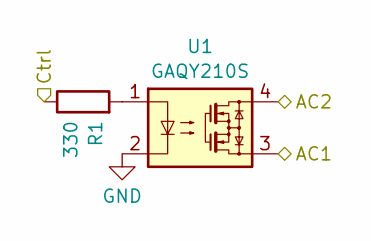
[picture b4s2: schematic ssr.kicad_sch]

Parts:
R1: 330; R_0603_1608Metric; LCSC Part # C23138
U1: GAQY210S; SOP-4_3.8x4.1mm_P2.54mm; LCSC Part # C7435113

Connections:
/AC0: U1.3; also elsewhere on the board
/AC_in: U1.4; also elsewhere on the board
/SSR/Ctrl: R1.1; also elsewhere on the board
GND: U1.2; also elsewhere on the board
unnamed: R1.2, U1.1

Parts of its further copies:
R2, R3, R4, R5, R6, R7, R8, R9, R10, R11, R12, R13, R14, R15, R16: 330; R_0603_1608Metric; LCSC Part # C23138
U2, U3, U4, U5, U6, U7, U8, U9, U10, U11, U12, U13, U14, U15, U16: GAQY210S; SOP-4_3.8x4.1mm_P2.54mm; LCSC Part # C7435113

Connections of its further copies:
/AC1: U2.3; also elsewhere on the board
/AC2: U3.3; also elsewhere on the board
/AC3: U4.3; also elsewhere on the board
/AC4: U5.3; also elsewhere on the board
/AC5: U6.3; also elsewhere on the board
/AC6: U7.3; also elsewhere on the board
/AC7: U8.3; also elsewhere on the board
/AC_in: U2.4, U3.4, U4.4, U5.4, U6.4, U7.4, U8.4, U9.4, U10.4, U11.4, U12.4, U13.4, U14.4, U15.4, U16.4; also elsewhere on the board
/SSR1/Ctrl: R2.1; also elsewhere on the board
/SSR2/Ctrl: R3.1; also elsewhere on the board
/SSR3/Ctrl: R4.1; also elsewhere on the board
/SSR4/Ctrl: R5.1; also elsewhere on the board
/SSR5/Ctrl: R6.1; also elsewhere on the board
/SSR6/Ctrl: R7.1; also elsewhere on the board
/SSR7/Ctrl: R8.1; also elsewhere on the board
/SSR8/AC1: U9.3; also elsewhere on the board
/SSR8/Ctrl: R9.1; also elsewhere on the board
/SSR9/AC1: U10.3; also elsewhere on the board
/SSR9/Ctrl: R10.1; also elsewhere on the board
/SSR10/AC1: U11.3; also elsewhere on the board
/SSR10/Ctrl: R11.1; also elsewhere on the board
/SSR11/AC1: U12.3; also elsewhere on the board
/SSR11/Ctrl: R12.1; also elsewhere on the board
/SSR12/AC1: U13.3; also elsewhere on the board
/SSR12/Ctrl: R13.1; also elsewhere on the board
/SSR13/AC1: U14.3; also elsewhere on the board
/SSR13/Ctrl: R14.1; also elsewhere on the board
/SSR14/AC1: U15.3; also elsewhere on the board
/SSR14/Ctrl: R15.1; also elsewhere on the board
/SSR15/AC1: U16.3; also elsewhere on the board
/SSR15/Ctrl: R16.1; also elsewhere on the board
GND: U2.2, U3.2, U4.2, U5.2, U6.2, U7.2, U8.2, U9.2, U10.2, U11.2, U12.2, U13.2, U14.2, U15.2, U16.2; also elsewhere on the board
unnamed: R2.2, U2.1
unnamed: R3.2, U3.1
unnamed: R4.2, U4.1
unnamed: R5.2, U5.1
unnamed: R6.2, U6.1
unnamed: R7.2, U7.1
unnamed: R8.2, U8.1
unnamed: R9.2, U9.1
unnamed: R10.2, U10.1
unnamed: R11.2, U11.1
unnamed: R12.2, U12.1
unnamed: R13.2, U13.1
unnamed: R14.2, U14.1
unnamed: R15.2, U15.1
unnamed: R16.2, U16.1

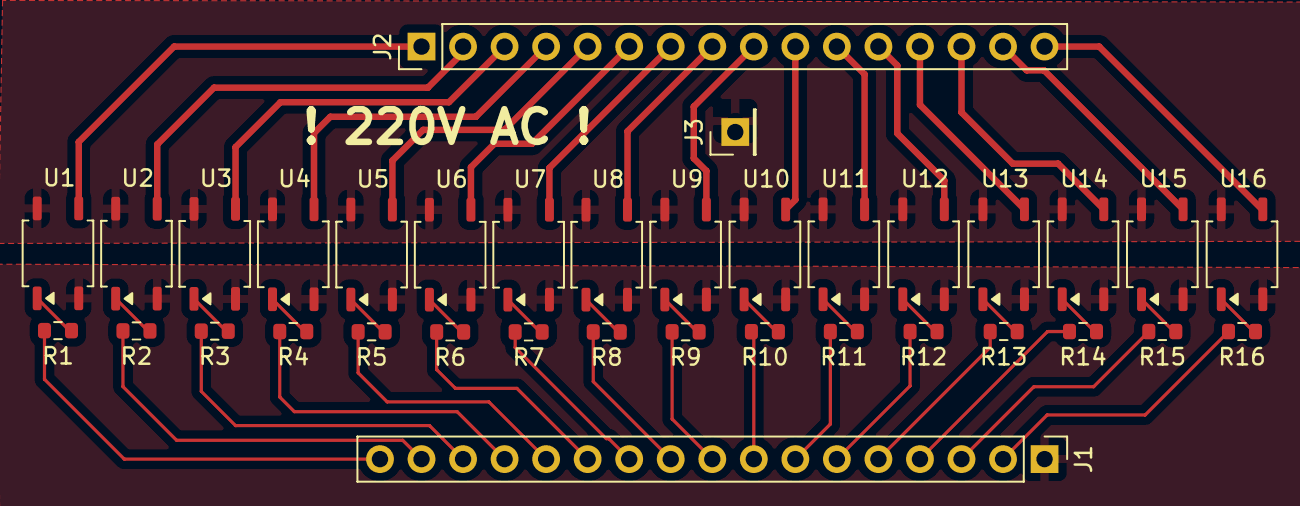
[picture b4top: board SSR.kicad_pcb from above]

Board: 2 copper layers, 35 parts (0 on the bottom side), 50 nets.

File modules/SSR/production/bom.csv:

Designator,Footprint,Quantity,Value,LCSC Part #
"R1, R10, R11, R12, R13, R14, R15, R16, R2, R3, R4, R5, R6, R7, R8, R9",0603,16,330,C23138
"U1, U10, U11, U12, U13, U14, U15, U16, U2, U3, U4, U5, U6, U7, U8, U9",SOP-4_3.8x4.1mm_P2.54mm,16,GAQY210S,C7435113
